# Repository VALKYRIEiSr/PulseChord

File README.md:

# PulseChord: Wearable Haptic/Vibrational Audio System
**OSHWA Certified Open Source Hardware | PK000001**

## Project Overview
PulseChord is a purely analog haptic feedback belt that converts live audio into tactile vibrations through voice coil actuators positioned around the torso/waist. Designed to create an immersive sensory experience, it delivers real-time feedback corresponding to musical rhythm and dynamics.

This project bridges the gap between digital audio and physical sensation, utilizing an industrial manufacturing substrate to create an accessible, wearable haptic interface.

## Press & Recognition
PulseChord was featured as Pakistan's first OSHWA-certified project in the January 2026 Open Source Hardware Certification roundup:
* **Make: Magazine** — [Open Source Hardware Certifications for January 2026](https://makezine.com/article/technology/open-source/open-source-hardware-certifications-for-january-2026/)
* **Hackster.io** — [January 2026 Open Source Hardware Certification Roundup](https://www.hackster.io/news/january-2026-open-source-hardware-certification-roundup-2705cc24ead9)

## Technical Research
The academic theory and signal-conditioning research behind this project can be found on SSRN:
* **SSRN Research Paper:** [PulseChord: Wearable Haptic Systems](https://papers.ssrn.com/sol3/papers.cfm?abstract_id=5532803) (Please refer to for more details)

## Technical Specifications
* **Architecture:** Purely Analog Signal Processing (No Software/Microcontroller)
* **Haptic Drivers:** 6x Full-range vibrational voice coil actuators (4Ω, 5W)
* **Amplification:** Dual TPA3110 (XHA232) Class D Stereo Amplifiers
* **Wiring Configuration:** Drivers are wired in **series pairs** (8Ω per pair) as shown in `Schematic 2.png`.
* **Conditioning:** TL074-based low-noise quad op-amp stage
* **Power:** 11.1V 3S LiPo Battery (2200mAh)
* **Chassis:** 50mm High-durability Nylon webbing with 3D-printed modular mounts
* **Fasteners:** M2 x 30mm Stainless Steel hardware

## Repository Structure
* `Hardware`: Eagle Schematic (`.sch`) and Board (`.brd`) files
* `Mechanical`: 3D source files (`.stl`, `.FCStd`) for speaker holders
* `BOM.txt`: Formatted Bill of Materials with manufacturer specifications
* `BOM.xlxs`: Formatted Bill of Materials with costs
* `LICENSE.txt`: Hardware (CERN-OHL-P-2.0) and Documentation (CC-BY-SA-4.0) licenses
* `GerberFiles.zip`: Production-ready files for PCB fabrication

## Assembly Quick-Start
1. **PCB:** Fabricate the Gerber files using a standard 2-layer FR4 process.
2. **Printing:** Print 6x `Holder Design-Body.stl` in PLA (20% infill).
3. **Mechanical Assembly:** First, mount the speakers into the 3D-printed holders using M2 x 30mm screws and nuts, as detailed in **Speaker.png**.
    * Once secured, thread the 50mm nylon strap through the integrated slots in the holders.
    * Finally, glue, staple, or stitch the velcro hook to one end and the velco loop to the other.
4. **Wiring:** Wire the speakers in series pairs as detailed in **Schematic 2.png**. Connect each 8Ω load to the amplifier output channels.

## Licensing
* **Hardware:** [CERN-OHL-P-2.0](https://spdx.org/licenses/CERN-OHL-P-2.0.html)
* **Documentation:** [CC-BY-SA-4.0](https://creativecommons.org/licenses/by-sa/4.0/)

---
**Developer:** Hariz Zoran Farooq
**Contact:** harizzoranfarooq@gmail.com
*Certified with the Open Source Hardware Association | PK000001.*

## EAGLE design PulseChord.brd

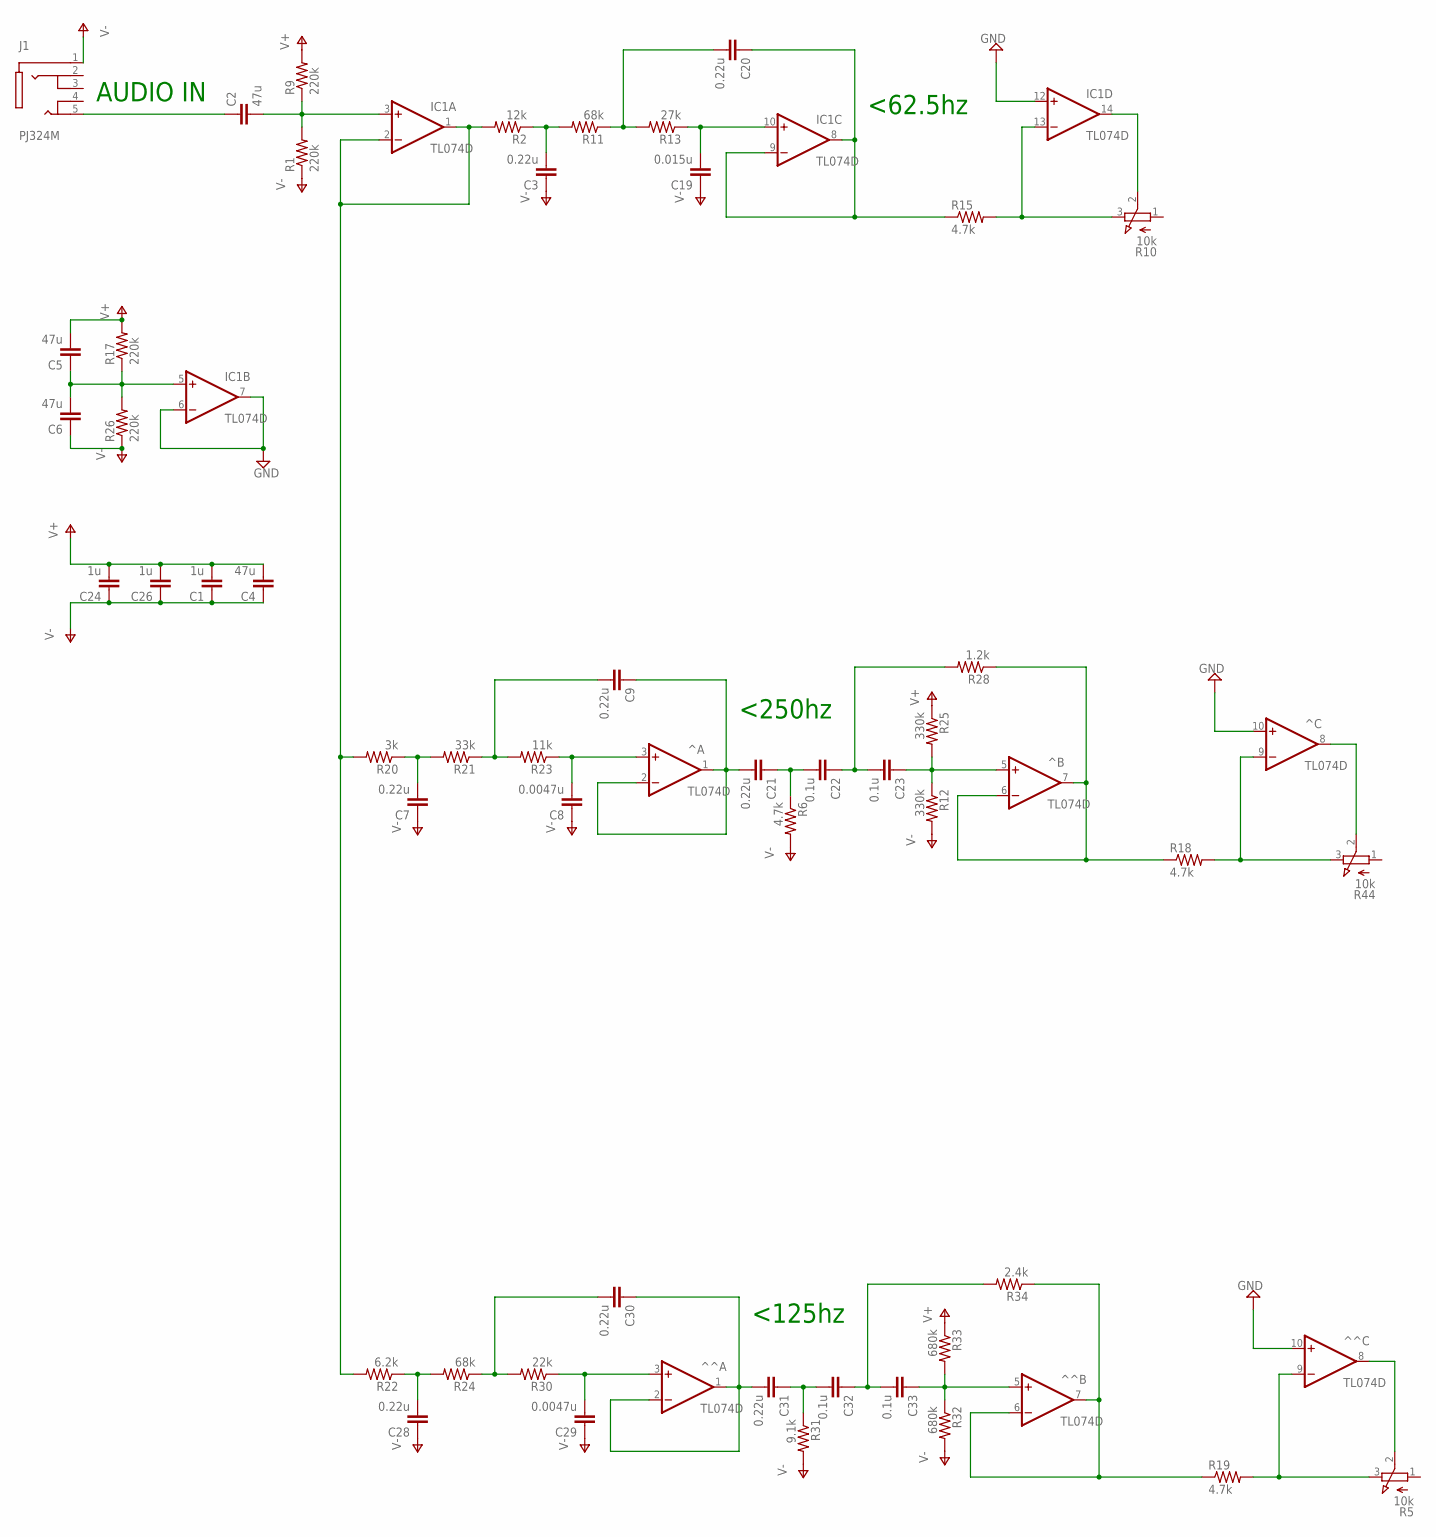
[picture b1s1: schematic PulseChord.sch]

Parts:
C1, C24, C26: 1u; C0603
C2, C4, C5, C6: 47u; C0603
C3, C7, C9, C20, C21, C28, C30, C31: 0.22u; C0603
C8, C29: 0.0047u; C0603
C19: 0.015u; C0603
C22, C23, C32, C33: 0.1u; C0603
IC1: TL074D; SO14
J1: PJ324M; WENZHOU_PJ324M
R1, R9, R17, R26: 220k; R0603
R2: 12k; R0603
R5, R10, R44: 10k; 3RP/1610N
R6, R15, R18, R19: 4.7k; R0603
R11, R24: 68k; R0603
R12, R25: 330k; R0603
R13: 27k; R0603
R20: 3k; R0603
R21: 33k; R0603
R22: 6.2k; R0603
R23: 11k; R0603
R28: 1.2k; R0603
R30: 22k; R0603
R31: 9.1k; R0603
R32, R33: 680k; R0603
R34: 2.4k; R0603
^: TL074D; SO14
^^: TL074D; SO14

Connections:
GND: IC1.6 (-IN), IC1.7 (OUT), IC1.12 (+IN), ^.10 (+IN), ^^.10 (+IN)
unnamed: IC1.1 (OUT), IC1.2 (-IN), R2.2, R20.2, R22.2
unnamed: C2.2, IC1.3 (+IN), R1.2, R9.1
unnamed: R5.3 (E), R19.2, ^^.9 (-IN)
unnamed: R5.2 (S), ^^.8 (OUT)
unnamed: C5.1, C6.2, IC1.5 (+IN), R17.1, R26.2
unnamed: C8.2, R23.1, ^.3 (+IN)
unnamed: IC1.13 (-IN), R10.3 (E), R15.2
unnamed: C9.2, R21.1, R23.2
unnamed: C3.2, R2.1, R11.2
unnamed: C2.1, J1.5 (TIP_2)
unnamed: C21.1, C22.2, R6.1
unnamed: C9.1, C21.2, ^.1 (OUT), ^.2 (-IN)
unnamed: C31.1, C32.2, R31.1
unnamed: C19.2, IC1.10 (+IN), R13.1
unnamed: C30.1, C31.2, ^^.1 (OUT), ^^.2 (-IN)
unnamed: C32.1, C33.2, R34.2
unnamed: C22.1, C23.2, R28.2
unnamed: C33.1, R32.1, R33.2, ^^.5 (+IN)
unnamed: C7.2, R20.1, R21.2
unnamed: R19.1, R34.1, ^^.6 (-IN), ^^.7 (OUT)
unnamed: C28.2, R22.1, R24.2
unnamed: IC1.14 (OUT), R10.2 (S)
unnamed: C20.2, R11.1, R13.2
unnamed: R18.2, R44.3 (E), ^.9 (-IN)
unnamed: C23.1, R12.1, R25.2, ^.5 (+IN)
unnamed: R44.2 (S), ^.8 (OUT)
unnamed: C30.2, R24.1, R30.2
unnamed: R18.1, R28.1, ^.6 (-IN), ^.7 (OUT)
unnamed: C20.1, IC1.8 (OUT), IC1.9 (-IN), R15.1
unnamed: C29.2, R30.1, ^^.3 (+IN)
V+: C1.2, C4.2, C5.2, C24.2, C26.2, IC1.4 (V+), R9.2, R17.2, R25.1, R33.1, ^.4 (V+), ^^.4 (V+)
V-: C1.1, C3.1, C4.1, C6.1, C7.1, C8.1, C19.1, C24.1, C26.1, C28.1, C29.1, IC1.11 (V-), J1.1 (SLEEVE), R1.1, R6.2, R12.2, R26.1, R31.2, R32.2, ^.11 (V-), ^^.11 (V-)

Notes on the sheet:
<250hz
<125hz
AUDIO IN
<62.5hz

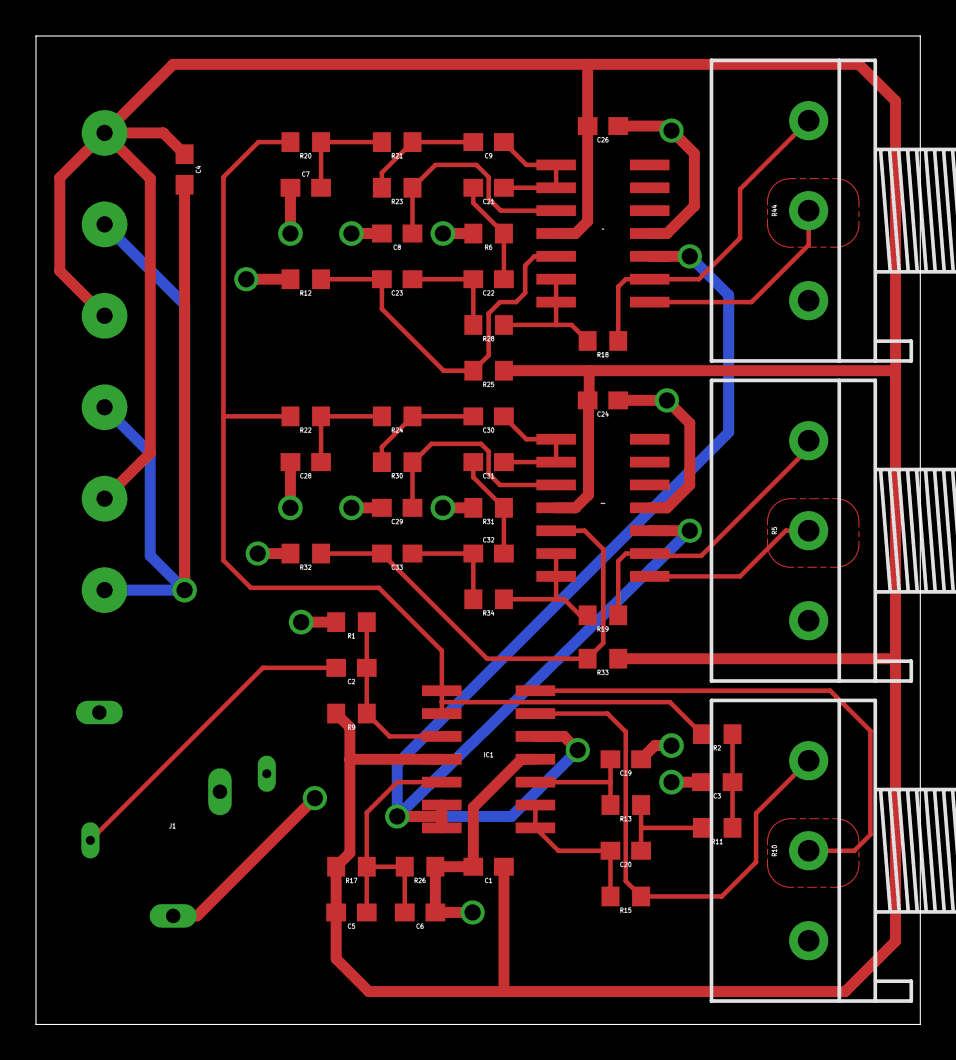
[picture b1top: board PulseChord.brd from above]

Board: 2 copper layers, 49.1 x 54.9 mm, 53 parts (1 on the bottom side), 33 nets.

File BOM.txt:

================================================================================
                       BILL OF MATERIALS: PULSECHORD
================================================================================
Project Status: OSHWA-Compliant Documentation
License:        CERN-OHL-P (Hardware), CC-BY-SA (Documentation)

1. SURFACE MOUNT DEVICES (PCB COMPONENTS)
--------------------------------------------------------------------------------
PART            VALUE       PACKAGE         DESCRIPTION
--------------------------------------------------------------------------------
C1, C24, C26    1u          C0603           Ceramic Capacitor
C2, C4-C6       47u         C0603           Ceramic Capacitor (Bulk)
C3, C7, C9      0.22u       C0603           Ceramic Capacitor
C20, C21        0.22u       C0603           Ceramic Capacitor
C28, C30, C31   0.22u       C0603           Ceramic Capacitor
C8, C29         0.0047u     C0603           Ceramic Capacitor
C19             0.015u      C0603           Ceramic Capacitor
C22, C23        0.1u        C0603           Ceramic Capacitor (Bypass)
C32, C33        0.1u        C0603           Ceramic Capacitor (Bypass)
IC1-IC3         TL074D      SO14            Low-Noise Quad Op-Amp
J1              PJ324M      PJ324M          3.5mm Stereo Audio Jack
R1, R9, R17     220k        R0603           Resistor
R26             220k        R0603           Resistor
R2              12k         R0603           Resistor
R5, R10, R44    10k         3RP/1610N       Potentiometer (Linear)
R6, R15, R18    4.7k        R0603           Resistor
R19             4.7k        R0603           Resistor
R11, R24        68k         R0603           Resistor
R12, R25        330k        R0603           Resistor
R13             27k         R0603           Resistor
R20             3k          R0603           Resistor
R21             33k         R0603           Resistor
R22             6.2k        R0603           Resistor
R23             11k         R0603           Resistor
R28             1.2k        R0603           Resistor
R30             22k         R0603           Resistor
R31             9.1k        R0603           Resistor
R32, R33        680k        R0603           Resistor
R34             2.4k        R0603           Resistor

2. AUDIO & POWER ELECTRONICS
--------------------------------------------------------------------------------
ITEM                    SPECIFICATION           QTY     NOTES
--------------------------------------------------------------------------------
Stereo Amplifier        TPA3110 (XHA232)        2       30W + 30W Class D
Full Range Speaker      4 Ohm, 5W               6       40mm Driver
LiPo Battery            2200mAh, 11.1V          1       3-Cell (3S) Pack

3. MECHANICALS & 3D ASSETS
--------------------------------------------------------------------------------
ITEM                    SPECIFICATION           QTY     SOURCE FILE
--------------------------------------------------------------------------------
Speaker Holder          3D Printed (PLA)        6       Holder Design-Body.stl
Fastener: Screw         M2 x 30mm               24      Socket Head Cap
Fastener: Nut           M2 Hex Nut              24      Standard M2 Metric
--------------------------------------------------------------------------------

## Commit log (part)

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2025-12-25 Rename Speakers.png to Schematic 2.png
2025-12-25 Rename Speaker Brace.png to Speaker.png
2025-12-25 Update and rename LICENSE.txt to LICENSE
2026-01-08 Update LICENSE
